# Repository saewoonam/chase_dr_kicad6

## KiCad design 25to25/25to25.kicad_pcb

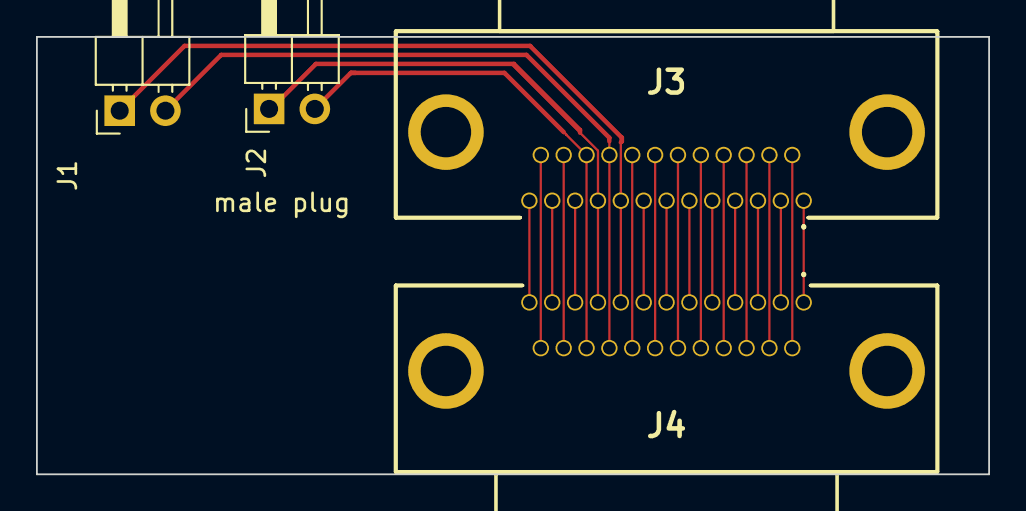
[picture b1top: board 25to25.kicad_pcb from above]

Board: 2 copper layers, 52.9 x 24.3 mm, 4 parts (0 on the bottom side), 25 nets.

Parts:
J1, J2: Conn_01x02_Male_2.54mm; PinHeader_1x02_P2.54mm_Horizontal
J3: DB25_Male_MountingHoles; 581M25113L461_Norcomp
J4: DB25_Female_MountingHoles; 581M25213L461_Norcomp_Female

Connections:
unnamed: J1.1, J3.9, J4.9
unnamed: J1.2, J3.22, J4.22
unnamed: J2.1, J3.10, J4.10
unnamed: J2.2, J3.23, J4.23
unnamed: J3.1, J4.1
unnamed: J3.2, J4.2
unnamed: J3.3, J4.3
unnamed: J3.4, J4.4
unnamed: J3.5, J4.5
unnamed: J3.6, J4.6
unnamed: J3.7, J4.7
unnamed: J3.8, J4.8
unnamed: J3.11, J4.11
unnamed: J3.12, J4.12
unnamed: J3.13, J4.13
unnamed: J3.14, J4.14
unnamed: J3.15, J4.15
unnamed: J3.16, J4.16
unnamed: J3.17, J4.17
unnamed: J3.18, J4.18
unnamed: J3.19, J4.19
unnamed: J3.20, J4.20
unnamed: J3.21, J4.21
unnamed: J3.24, J4.24
unnamed: J3.25, J4.25

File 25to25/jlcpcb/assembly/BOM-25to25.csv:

Comment,Designator,Footprint,LCSC
Conn_01x02_Male_2.54mm,"J1,J2",PinHeader_1x02_P2.54mm_Horizontal,C706865
DB25_Female_MountingHoles,J4,581M25213L461_Norcomp_Female,
DB25_Male_MountingHoles,J3,581M25113L461_Norcomp,

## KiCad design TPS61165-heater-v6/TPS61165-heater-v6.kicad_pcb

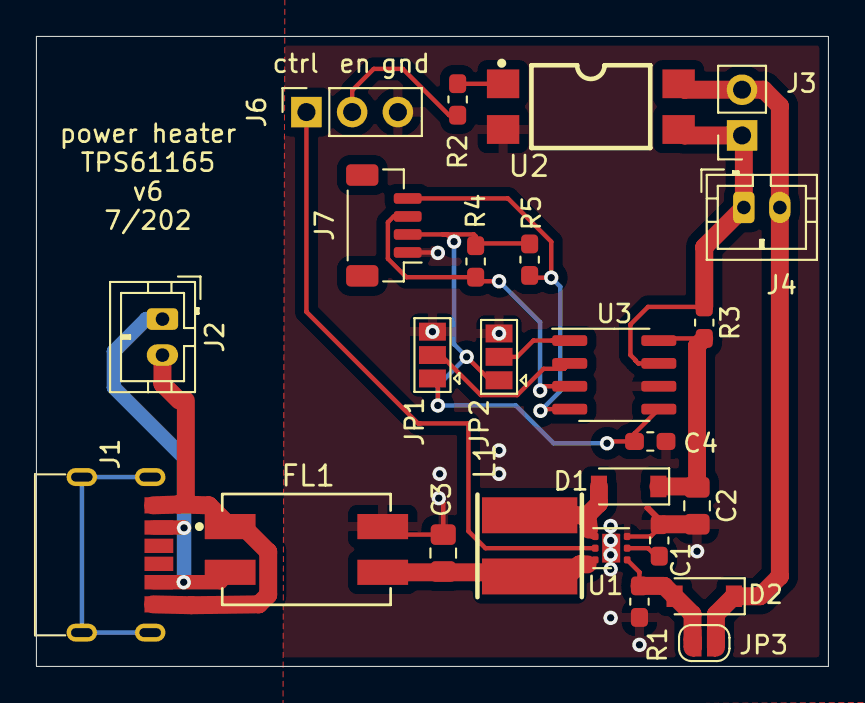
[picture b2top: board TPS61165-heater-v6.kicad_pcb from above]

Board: 2 copper layers, 44.0 x 35.0 mm, 25 parts (0 on the bottom side), 18 nets.

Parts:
C1: 220nF; C_0603_1608Metric_Pad1.05x0.95mm_HandSolder
C2: 1uF_0805_50V; C_0805_2012Metric_Pad1.15x1.40mm_HandSolder
C3: 4.7uF_0805_25V; C_0805_2012Metric_Pad1.15x1.40mm_HandSolder
C4: 100nF; C_0603_1608Metric_Pad1.05x0.95mm_HandSolder
D1: MBR0540; D_SOD-123
D2: BZT52C5V1; D_SOD-123
FL1: EMI_Filter_LL; LL_FILTER-SMD_4P-L9.2-W6.0-TL
J1: USB_C_KoreanHroparts_6P; my_HRO-TYPE-C-31-M-17
J2, J4: A2001WV-2P; JST_PH_B2B-PH-K_1x02_P2.00mm_Vertical
J3: Conn_01x02_Female; PinSocket_1x02_P2.54mm_Vertical
J6: Conn_01x03_Female; PinSocket_1x03_P2.54mm_Vertical
J7: A1001WV-S-04P; JST_SH_BM04B-SRSS-TB_1x04-1MP_P1.00mm_Vertical
JP1, JP2: Jumper_3_Open; SolderJumper-3_P1.3mm_Open_Pad1.0x1.5mm
JP3: Jumper_2_Open; SolderJumper-2_P1.3mm_Open_RoundedPad1.0x1.5mm
L1: 10uH; IND-SMD_L4.7-W4.7
R1, R3: 1; R_0603_1608Metric_Pad1.05x0.95mm_HandSolder
R2: 390; R_0603_1608Metric_Pad1.05x0.95mm_HandSolder
R4, R5: 4.99K; R_0603_1608Metric_Pad1.05x0.95mm_HandSolder
U1: TPS61165; WSON-6-1EP_2x2mm_P0.65mm_EP1x1.6mm
U2: KAQY212A; SMD-4_L4.6-W6.4-P2.54-LS10.0-BR
U3: INA219AxD; SOIC-8_3.9x4.9mm_P1.27mm

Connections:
+5VD: C3.1, FL1.3, L1.1, U1.6 (VIN)
/scl: J7.4 (SCL), R5.1, U3.4 (SCL)
/sda: J7.3 (SDA), R4.1, U3.3 (SDA)
GND: C1.2, C2.2, C3.2, C4.2, FL1.4, J6.3, J7.1 (gnd), JP1.3 (B), JP2.3 (B), R1.2, U1.3 (GND), U1.7 (EP), U2.2, U3.6 (GND)
unnamed: C1.1, U1.2 (COMP)
unnamed: C2.1, D1.1 (K), R3.2, U3.8 (IN+)
unnamed: C4.1, J7.2 (VCC), JP1.1 (A), JP2.1 (A), R4.2, R5.2, U3.5 (VS)
unnamed: D1.2 (A), L1.2, U1.4 (SW)
unnamed: D2.1 (K), J3.2, J4.2 (-), JP3.2 (B), U2.4
unnamed: D2.2 (A), JP3.1 (A), R1.1, U1.1 (FB)
unnamed: FL1.1, J1.A12 (GND), J1.B12 (GND), J2.2 (-)
unnamed: FL1.2, J1.A9 (VBUS), J1.B9 (VBUS), J2.1 (+)
unnamed: J3.1, J4.1 (+), R3.1, U2.3, U3.7 (IN-)
unnamed: J6.1, U1.5 (CTRL)
unnamed: J6.2, R2.1
unnamed: JP1.2 (C), U3.2 (A0)
unnamed: JP2.2 (C), U3.1 (A1)
unnamed: R2.2, U2.1

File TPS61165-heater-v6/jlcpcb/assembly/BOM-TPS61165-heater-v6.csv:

Comment,Designator,Footprint,LCSC
TPS61165,U1,WSON-6-1EP_2x2mm_P0.65mm_EP1x1.6mm,C122568
INA219AxD,U3,SOIC-8_3.9x4.9mm_P1.27mm,C138706
Conn_01x03_Female,J6,PinSocket_1x03_P2.54mm_Vertical,C146243
100nF,C4,C_0603_1608Metric_Pad1.05x0.95mm_HandSolder,C14663
BZT52C5V1,D2,D_SOD-123,C173407
KAQY212A,U2,SMD-4_L4.6-W6.4-P2.54-LS10.0-BR,C194713
220nF,C1,C_0603_1608Metric_Pad1.05x0.95mm_HandSolder,C21120
MBR0540,D1,D_SOD-123,C21353
A2001WV-2P,"J2,J4",JST_PH_B2B-PH-K_1x02_P2.00mm_Vertical,C225188
1,"R1,R3",R_0603_1608Metric_Pad1.05x0.95mm_HandSolder,C22936
4.99K,"R4,R5",R_0603_1608Metric_Pad1.05x0.95mm_HandSolder,C23046
390,R2,R_0603_1608Metric_Pad1.05x0.95mm_HandSolder,C23151
EMI_Filter_LL,FL1,LL_FILTER-SMD_4P-L9.2-W6.0-TL,C261397
1uF_0805_50V,C2,C_0805_2012Metric_Pad1.15x1.40mm_HandSolder,C28323
USB_C_KoreanHroparts_6P,J1,my_HRO-TYPE-C-31-M-17,C283540
4.7uF_0805_25V,C3,C_0805_2012Metric_Pad1.15x1.40mm_HandSolder,C354262
A1001WV-S-04P,J7,JST_SH_BM04B-SRSS-TB_1x04-1MP_P1.00mm_Vertical,C371588
Conn_01x02_Female,J3,PinSocket_1x02_P2.54mm_Vertical,C49661
10uH,L1,IND-SMD_L4.7-W4.7,C89448

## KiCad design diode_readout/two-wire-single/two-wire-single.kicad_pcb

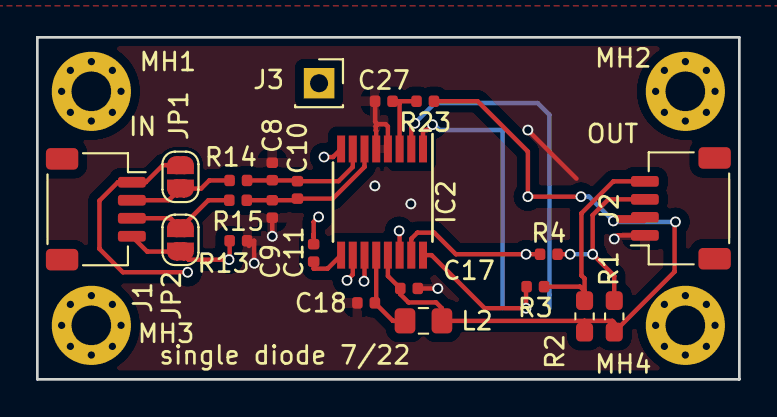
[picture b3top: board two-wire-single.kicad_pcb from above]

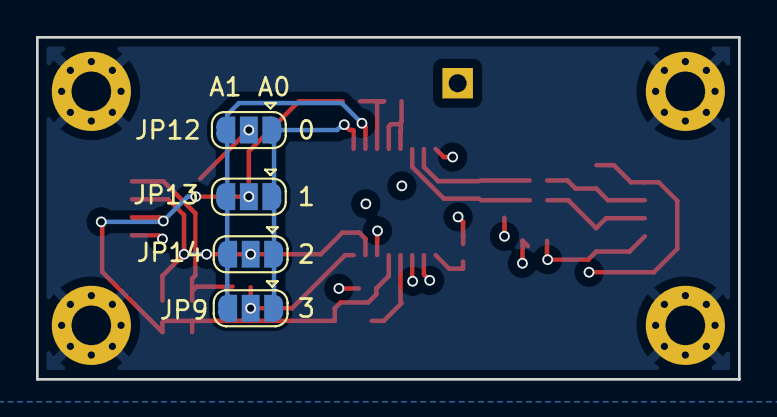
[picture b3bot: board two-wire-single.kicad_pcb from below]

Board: 4 copper layers, 39.0 x 19.0 mm, 30 parts (4 on the bottom side), 20 nets.

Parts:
C8, C9, C11, C17, C18, C27: 100nF; C_0402_1005Metric
C10: 1uF; C_0402_1005Metric
IC2: ADS112C04IPWR; TSSOP-16_4.4x5mm_P0.65mm
J1: Conn_01x04; JST_SH_SM04B-SRSS-TB_1x04-1MP_P1.00mm_Horizontal
J2: JST_SH_Conn_01x04_i2c_horizontal; JST_SH_SM04B-SRSS-TB_1x04-1MP_P1.00mm_Horizontal
J3: Conn_01x01_Female; PinSocket_1x01_P2.54mm_Vertical
JP1, JP2: Jumper_NO_Small; SolderJumper-2_P1.3mm_Open_RoundedPad1.0x1.5mm
JP9, JP12, JP13, JP14: Jumper_3_Open; SolderJumper-3_P1.3mm_Open_RoundedPad1.0x1.5mm
L2: MMZ2012Y202B; L_0805_2012Metric_Pad1.15x1.40mm_HandSolder
MH1, MH2, MH3, MH4: MountingHole; MountingHole_2.2mm_M2_Pad_Via
R1, R2: 10K; R_0603_1608Metric_Pad1.05x0.95mm_HandSolder
R3, R4: 47; R_0402_1005Metric
R13: 10K 0.1%; R_0402_1005Metric
R14, R15: 100K; R_0402_1005Metric
R23: 1K; R_0402_1005Metric

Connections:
/Channel1/A0: IC2.1 (A0), JP9.1 (A), JP12.1 (A), JP13.1 (A), JP14.1 (A)
/Channel1/A1: IC2.2 (A1), JP9.3 (B), JP12.3 (B), JP13.3 (B), JP14.3 (B)
/Channel1/AIN0: IC2.11 (AIN0), J1.1, JP1.1
/Channel1/AIN1: IC2.10 (AIN1), J1.4, JP2.2, R13.1
/Channel1/V+: J1.2, JP1.2, R14.2
/Channel1/V-: J1.3, JP2.1, R15.2
/Channel1/Vpower: C18.2, IC2.12 (AVDD), L2.2
/Channel1/scl: IC2.16 (SCL), JP9.2 (C), R3.2
/Channel1/sda: IC2.15 (SDA), JP14.2 (C), R4.1
/Channel1/~DRDY: IC2.14 (~DRDY), J3.1
/scl-rx: J2.4 (SCL), R2.2, R3.1
/sda-tx: J2.3 (SDA), R1.2, R4.2
GND: C8.1, C9.2, C17.2, C18.1, C27.1, IC2.4 (DGND), IC2.5 (AVSS), J2.1 (gnd), JP12.2 (C), R13.2
GNDPWR: MH1.1, MH2.1, MH3.1, MH4.1
unnamed: C8.2, C10.1, IC2.7 (AIN2), R14.1
unnamed: C9.1, C10.2, IC2.6 (AIN3), R15.1
unnamed: C11.1, IC2.9 (REFP)
unnamed: C11.2, IC2.8 (REFN)
unnamed: C27.2, IC2.3 (~RESET), R23.2
VD: C17.1, IC2.13 (DVDD), J2.2 (VCC), JP13.2 (C), L2.1, R1.1, R2.1, R23.1

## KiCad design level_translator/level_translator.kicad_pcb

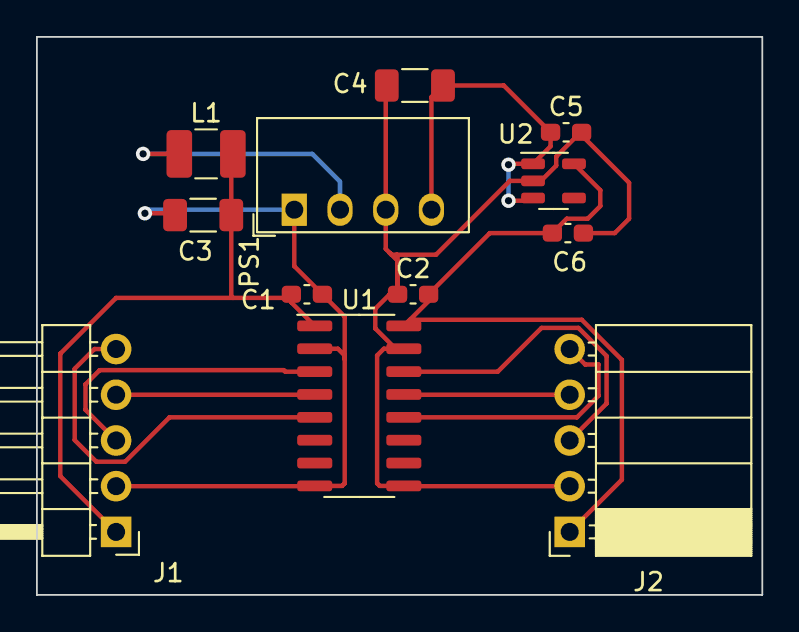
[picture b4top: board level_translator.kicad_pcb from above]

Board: 2 copper layers, 40.3 x 31.0 mm, 12 parts (0 on the bottom side), 12 nets.

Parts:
C1, C2: 100nF; C_0603_1608Metric_Pad1.08x0.95mm_HandSolder
C3: 4.7uF; C_1206_3216Metric_Pad1.33x1.80mm_HandSolder
C4: 10uF; C_1206_3216Metric_Pad1.33x1.80mm_HandSolder
C5, C6: 1uF; C_0603_1608Metric_Pad1.08x0.95mm_HandSolder
J1: Conn_01x05_Male; PinHeader_1x05_P2.54mm_Horizontal
J2: Conn_01x05_Female; PinSocket_1x05_P2.54mm_Horizontal
L1: 6.8uF; L_1210_3225Metric_Pad1.42x2.65mm_HandSolder
PS1: B0305S-1WR2; Converter_DCDC_Murata_CRE1xxxxxx3C_THT
U1: pi141x3x; SOIC-16_3.9x9.9mm_P1.27mm
U2: SOT-23-5

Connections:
+5V: C2.2, C6.1, J2.1, U1.16 (VCC2), U2.5 (OUT)
GND: C2.1, C4.2, C5.2, C6.2, J2.2, PS1.3 (0V), U1.9 (GND2), U1.11 (IND), U1.15 (GND2), U2.2 (GND)
GNDPWR: C1.1, C3.2, J1.2, PS1.1 (-Vin), U1.2 (GND1), U1.8 (GND1)
unnamed: C4.1, C5.1, PS1.4 (+Vout), U2.1 (IN), U2.3 (EN)
unnamed: J1.3, U1.3 (INA)
unnamed: J1.4, U1.4 (INB)
unnamed: J1.5, U1.5 (INC)
unnamed: J2.3, U1.14 (OUTA)
unnamed: J2.4, U1.13 (OUTB)
unnamed: J2.5, U1.12 (OUTC)
unnamed: L1.1, PS1.2 (+Vin)
VD: C1.2, C3.1, J1.1, L1.2, U1.1 (VCC1)

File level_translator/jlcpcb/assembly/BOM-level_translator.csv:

Comment,Designator,Footprint,LCSC
10uF,C4,C_1206_3216Metric_Pad1.33x1.80mm_HandSolder,C13585
Conn_01x05_Male,J1,PinHeader_1x05_P2.54mm_Horizontal,C138801
100nF,"C1,C2",C_0603_1608Metric_Pad1.08x0.95mm_HandSolder,C14663
1uF,"C5,C6",C_0603_1608Metric_Pad1.08x0.95mm_HandSolder,C15849
4.7uF,C3,C_1206_3216Metric_Pad1.33x1.80mm_HandSolder,C29823
Conn_01x05_Female,J2,PinSocket_1x05_P2.54mm_Horizontal,C35167
pi141x3x,U1,SOIC-16_3.9x9.9mm_P1.27mm,C471602
~,U2,SOT-23-5,C529554
B0305S-1WR2,PS1,Converter_DCDC_Murata_CRE1xxxxxx3C_THT,C80854
6.8uF,L1,L_1210_3225Metric_Pad1.42x2.65mm_HandSolder,C87559

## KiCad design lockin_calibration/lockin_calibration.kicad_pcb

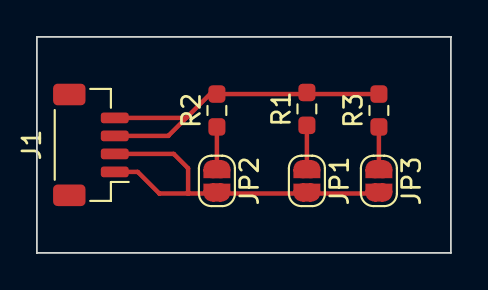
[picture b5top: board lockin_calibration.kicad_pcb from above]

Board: 2 copper layers, 23.0 x 12.0 mm, 7 parts (0 on the bottom side), 5 nets.

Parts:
J1: JST_SRSS_Conn_01x04_bridge_horizontal_2; JST_SH_BM04B-SRSS-TB_1x04-1MP_P1.00mm_Vertical
JP1, JP2, JP3: Jumper_2_Open; SolderJumper-2_P1.3mm_Open_RoundedPad1.0x1.5mm
R1: 20K_0.1%; R_0603_1608Metric_Pad0.98x0.95mm_HandSolder
R2: 1K 0.1%; R_0603_1608Metric_Pad0.98x0.95mm_HandSolder
R3: 10K 0.05%; R_0603_1608Metric_Pad0.98x0.95mm_HandSolder

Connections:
unnamed: J1.1 (I+), J1.2 (V+), JP1.2 (B), JP2.2 (B), JP3.2 (B)
unnamed: J1.3 (V-), J1.4 (I-), R1.2, R2.2, R3.2
unnamed: JP1.1 (A), R1.1
unnamed: JP2.1 (A), R2.1
unnamed: JP3.1 (A), R3.1

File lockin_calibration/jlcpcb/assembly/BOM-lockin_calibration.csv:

Comment,Designator,Footprint,LCSC
1K 0.1%,R2,R_0603_1608Metric_Pad0.98x0.95mm_HandSolder,C328422
JST_SRSS_Conn_01x04_bridge_horizontal_2,J1,JST_SH_BM04B-SRSS-TB_1x04-1MP_P1.00mm_Vertical,C371571
10K 0.05%,R3,R_0603_1608Metric_Pad0.98x0.95mm_HandSolder,C374378
20K_0.1%,R1,R_0603_1608Metric_Pad0.98x0.95mm_HandSolder,C53197

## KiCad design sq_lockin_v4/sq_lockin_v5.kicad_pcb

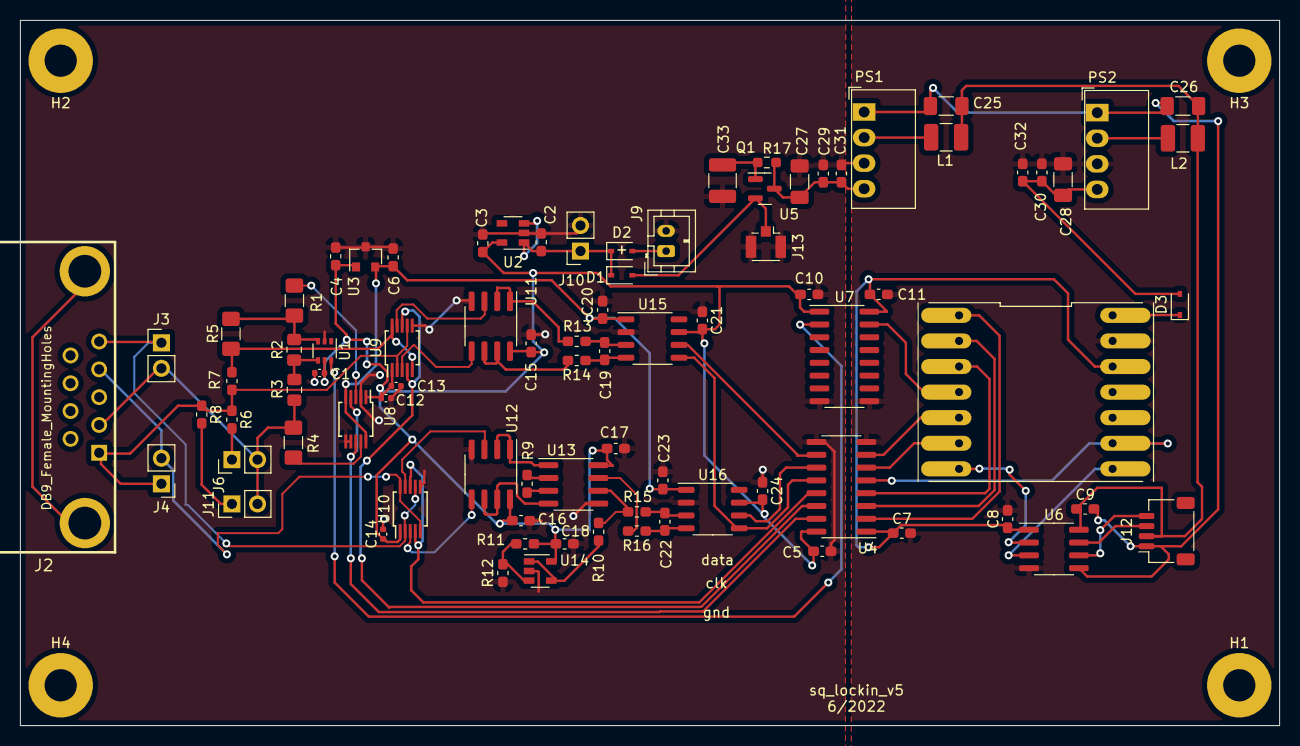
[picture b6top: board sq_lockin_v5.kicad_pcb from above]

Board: 2 copper layers, 125.0 x 70.0 mm, 87 parts (0 on the bottom side), 63 nets.

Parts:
C1, C12, C13, C14: 100nF_0402; C_0402_1005Metric
C2, C3, C4, C6: 1uF; C_0603_1608Metric_Pad1.05x0.95mm_HandSolder
C5, C7, C8, C9, C10, C11, C15, C16, C17, C18, C19, C20, C21, C22, C23, C24, C29, C30: 100nF; C_0603_1608Metric_Pad1.08x0.95mm_HandSolder
C25, C26: 4.7uF_1206_50V; C_1206_3216Metric_Pad1.33x1.80mm_HandSolder
C27, C28: 10uF_1206_50V; C_1206_3216Metric_Pad1.33x1.80mm_HandSolder
C31, C32: 10nF; C_0603_1608Metric_Pad1.08x0.95mm_HandSolder
C33: 47uF; C_1210_3225Metric_Pad1.33x2.70mm_HandSolder
D1, D2, D3: LBAT54HT1G; D_SOD-323
H1, H2, H3, H4: MountingHole; MountingHole_3.2mm_M3_Pad
J2: DB9_Female_MountingHoles; DSUB-TH_DS1037-09FNAKT74-0CC
J3, J4, J6, J11: Conn_01x02_Male_2.54mm; PinHeader_1x02_P2.54mm_Vertical
J9: battery; JST_PH_B2B-PH-K_1x02_P2.00mm_Vertical
J10: receptacle; PinSocket_1x02_P2.54mm_Vertical
J12: JST_SH_Conn_01x04_i2c_horizontal; JST_SH_SM04B-SRSS-TB_1x04-1MP_P1.00mm_Horizontal
J13: Conn_Coaxial; U.FL_Hirose_U.FL-R-SMT-1_Vertical
L1, L2: 6.8uH; L_1210_3225Metric_Pad1.42x2.65mm_HandSolder
PS1, PS2: B0305S-1WR2-0my_power; Converter_DCDC_Murata_MEE1SxxxxSC_THT
Q1: BC847C; SOT-23
R1, R4, R5: 1M_0.1%; R_1206_3216Metric_Pad1.42x1.75mm_HandSolder
R2: 75K_0.1%; R_0805_2012Metric_Pad1.15x1.40mm_HandSolder
R3: 5K_0.1%; R_0805_2012Metric_Pad1.15x1.40mm_HandSolder
R6: 10K 0.1%; R_0603_1608Metric_Pad1.05x0.95mm_HandSolder
R7: 100K_0.1%; R_0603_1608Metric_Pad1.05x0.95mm_HandSolder
R8: 1K 0.1%; R_0603_1608Metric_Pad1.05x0.95mm_HandSolder
R9: 5.49K; R_0603_1608Metric_Pad1.05x0.95mm_HandSolder
R10: 10; R_0603_1608Metric_Pad1.05x0.95mm_HandSolder
R11, R12: 10K; R_0603_1608Metric_Pad1.05x0.95mm_HandSolder
R13, R14, R15, R16: 100; R_0603_1608Metric_Pad1.05x0.95mm_HandSolder
R17: 1K; R_0603_1608Metric_Pad0.98x0.95mm_HandSolder
U1: NC7SB3157P6X; SOT-363_SC-70-6
U2: LP5907MFX-3.3; SOT-23-5
U3: REF3325; SOT-23
U4: pi162U; SOIC-16_3.9x9.9mm_P1.27mm
U5: seeed_rp2040; DIP-XIAO-QTPY
U6: PI121; SOIC-8_3.9x4.9mm_P1.27mm
U7: ISO7760DBQ; SOIC-16_3.9x9.9mm_P1.27mm
U8, U9, U10: RS2105XN; MSOP-10_3x3mm_P0.5mm
U11, U12: OPA2376xxDGK; SOIC-8_3.9x4.9mm_P1.27mm
U13: INA826; SOIC-8_3.9x4.9mm_P1.27mm
U14: OPA333xxDBV; SOT-23-5
U15, U16: HX710C; SOP-8_3.9x4.9mm_P1.27mm

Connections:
+3V3: C1.1, C3.1, C4.1, C5.1, C10.1, C12.1, C13.1, C14.1, C15.1, C16.1, C17.2, C18.1, C21.2, C24.2, R11.1, U1.5 (V+), U2.5 (OUT), U3.1 (IN), U4.16 (Vcc2), U7.1 (Vcc1), U8.1 (VCC), U9.1 (VCC), U10.1 (VCC), U11.8 (V+), U12.8 (V+), U13.8 (Vs+), U14.5 (V+), U15.7 (DVDD), U16.7 (DVDD)
+5VD: D3.1 (K), U5.14 (5V)
/I+: J2.1, J4.1, R6.1, R7.1, R8.1, U9.2, U9.7
/I-: J2.2, J3.2, J6.2, J11.2, R3.2, R4.2
/MC3.3: C7.1, C8.1, C11.1, U4.1 (Vcc1), U5.12 (3V3), U6.1 (VDD1), U7.16 (Vcc2)
/Sheet621A3D16/in+: U9.3, U11.5 (+)
/Sheet621A3D16/in-: U9.9, U11.3 (+)
/Sheet624B5D4E/ctrl+: U4.14 (OUTB), U9.4, U9.8
/Sheet624B5D4E/in+: R5.1, R7.2, U9.5, U9.10
/Sheet6275CBF8/in+: U10.3, U12.5 (+)
/Sheet6275CBF8/in-: U10.9, U12.3 (+)
/Sheet62237673/Clk_in: U4.12 (OUTD), U15.5 (PD_SCK), U16.5 (PD_SCK)
/Sheet62237673/Dout: U4.10 (INF), U15.6 (DOUT)
/Sheet62237673/V+: R14.2, U11.6 (-), U11.7
/Sheet62237673/V-: R13.2, U11.1, U11.2 (-)
/V+: J2.4, J4.2, U10.5, U10.10
/V-: J2.5, J3.1, U10.2, U10.7
/analog: D1.2 (A), J13.1 (In), Q1.2 (E)
/power/digital: C28.1, C30.2, C32.2, D3.2 (A), PS2.4 (+Vout)
/rx: U5.8 (P1), U6.3 (VOB)
/sheet624D2E57/Dout: U4.11 (INE), U16.6 (DOUT)
/sheet624D2E57/V+: R16.2, U13.7
/sheet624D2E57/V-: R10.2, R15.2, U13.6 (Ref)
/sheet624D2E58/ctrl+: U4.13 (OUTC), U10.4, U10.8
/sheet6256EE2A/ctrl+: U4.15 (OUTA), U8.4, U8.8
/sheet6256EE2A/out+: R1.2, U8.3
/sheet6256EE2A/out-: R4.1, U8.9
/tx: U5.7 (P0), U6.2 (VIA)
/vref: C6.1, C20.1, C23.1, U3.2 (OUT), U8.5, U8.10, U15.1 (VREF), U16.1 (VREF)
GND: C1.2, C2.2, C3.2, C4.2, C5.2, C6.2, C10.2, C12.2, C13.2, C14.2, C15.2, C16.2, C17.1, C18.2, C20.2, C21.1, C23.2, C24.1, C27.2, C29.1, C31.1, C33.2, J9.2 (-), J10.2, J13.2 (Ext), PS1.3 (0V), R12.2, U1.2 (GND), U2.2 (GND), U3.3 (GND), U4.9 (GND2), U7.8 (GND1), U8.2, U8.6 (GND), U8.7, U9.6 (GND), U10.6 (GND), U11.4 (V-), U12.4 (V-), U13.5 (Vs-), U14.2 (V-), U15.2 (AGND), U16.2 (AGND)
GNDD: C7.2, C8.2, C11.2, C28.2, C30.1, C32.1, PS2.3 (0V), U4.8 (GND1), U5.13 (GND), U6.4 (GND1), U7.9 (GND2)
GNDPWR: C9.2, C25.2, C26.2, J12.1 (gnd), PS1.1 (-Vin), PS2.1 (-Vin), U6.5 (GND2)
unnamed: C2.1, D1.1 (K), D2.1 (K), J10.1, U2.1 (IN), U2.3 (EN)
unnamed: C19.1, R14.1, U15.4 (INP)
unnamed: C19.2, R13.1, U15.3 (INN)
unnamed: C22.1, R16.1, U16.4 (INP)
unnamed: C22.2, R15.1, U16.3 (INN)
unnamed: C27.1, C29.2, C31.2, PS1.4 (+Vout), Q1.3 (C), R17.1
unnamed: C33.1, Q1.1 (B), R17.2
unnamed: D2.2 (A), J9.1 (+)
unnamed: U1.6, U7.2 (INA)
unnamed: J6.1, R6.2
unnamed: J11.1, R8.2
unnamed: J12.3 (SDA), U6.7 (VOA)
unnamed: J12.4 (SCL), U6.6 (VIB)
unnamed: L1.1, PS1.2 (+Vin)
unnamed: L2.1, PS2.2 (+Vin)
unnamed: R1.1, R2.1, R5.2, U1.3
unnamed: R2.2, R3.1, U1.4
unnamed: R9.1, U13.2 (Rg)
unnamed: R9.2, U13.3 (Rg)
unnamed: R10.1, U14.1, U14.4 (-)
unnamed: R11.2, R12.1, U14.3 (+)
unnamed: U4.2 (INA), U5.1 (P26)
unnamed: U4.3 (INB), U5.2 (P27)
unnamed: U4.4 (INC), U5.3 (P28)
unnamed: U4.5 (IND), U5.9 (P2)
unnamed: U4.6 (OUTE), U5.6 (P7)
unnamed: U4.7 (OUTF), U5.5 (P6)
unnamed: U5.4 (P29), U7.15 (OUTA)
unnamed: U12.1, U12.2 (-), U13.1 (-)
unnamed: U12.6 (-), U12.7, U13.4 (+)
VD: C9.1, C25.1, C26.1, J12.2 (VCC), L1.2, L2.2, U6.8 (VDD2)
